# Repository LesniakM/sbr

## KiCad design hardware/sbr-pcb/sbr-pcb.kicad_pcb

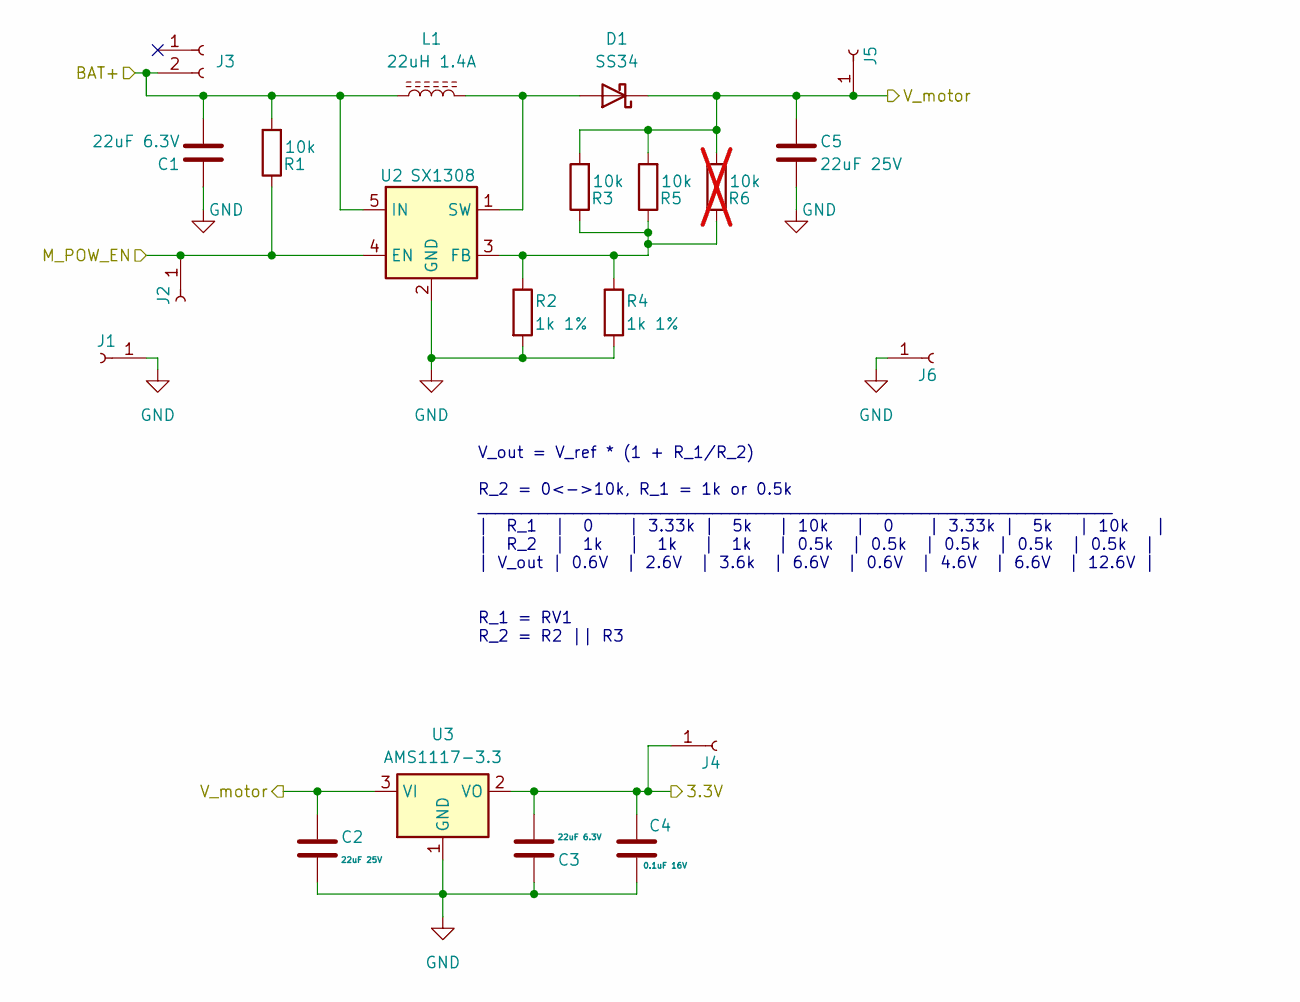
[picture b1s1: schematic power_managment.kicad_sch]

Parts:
C1, C3: 22uF 6.3V; C_0603_1608Metric; JLCPCB# C59461
C2, C5: 22uF 25V; C_0805_2012Metric; JLCPCB# C45783
C4: 0.1uF 16V; C_0402_1005Metric; JLCPCB# C1525
D1: SS34; D_SMA; JLCPCB# C8678
J1, J2, J4, J5, J6: Conn_hole; PinHeader_1x01_P2.54mm_Vertical
J3: Conn_01x02_Socket; PinHeader_1x02_P2.54mm_Vertical
L1: 22uH 1.4A; L_TDK_VLS6045EX_VLS6045AF; JLCPCB# C241601
R1, R3, R5: 10k; R_0603_1608Metric; JLCPCB# C25804
R2, R4: 1k 1%; R_0603_1608Metric; JLCPCB# C21190
R6: 10k; R_0603_1608Metric; JLCPCB# C25804; not fitted
U2: SX1308; SOT-23-6; LCSC Part # C78162
U3: AMS1117-3.3; SOT-223-3_TabPin2; JLCPCB# C6186

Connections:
/IMU/3.3V: C3.2, C4.1, J4.1, U3.2 (VO); also elsewhere on the board
/MCU/BAT+: C1.2, J3.2, L1.1, R1.2, U2.5 (IN); also elsewhere on the board
/MCU/M_POW_EN: J2.1, R1.1, U2.4 (EN); also elsewhere on the board
/motor_control/V_motor: C2.1, C5.1, D1.1 (K), J5.1, R3.2, R5.2, R6.2, U3.3 (VI); also elsewhere on the board
GND: C1.1, C2.2, C3.1, C4.2, C5.2, J1.1, J6.1, R2.2, R4.2, U2.2 (GND), U3.1 (GND); also elsewhere on the board
unnamed: D1.2 (A), L1.2, U2.1 (SW)
unnamed: R2.1, R3.1, R4.1, R5.1, R6.1, U2.3 (FB)

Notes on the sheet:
V_out = V_ref * (1 + R_1/R_2) R_2 = 0<->10k, R_1 = 1k or 0.5k _________________________________________________________________________ | R_1 | 0 | 3.33k | 5k | 10k | 0 | 3.33k | 5k | 10k | | R_2 | 1k | 1k | 1k | 0.5k | 0.5k | 0.5k | 0.5k | 0.5k | | V_out | 0.6V | 2.6V | 3.6k | 6.6V | 0.6V | 4.6V |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

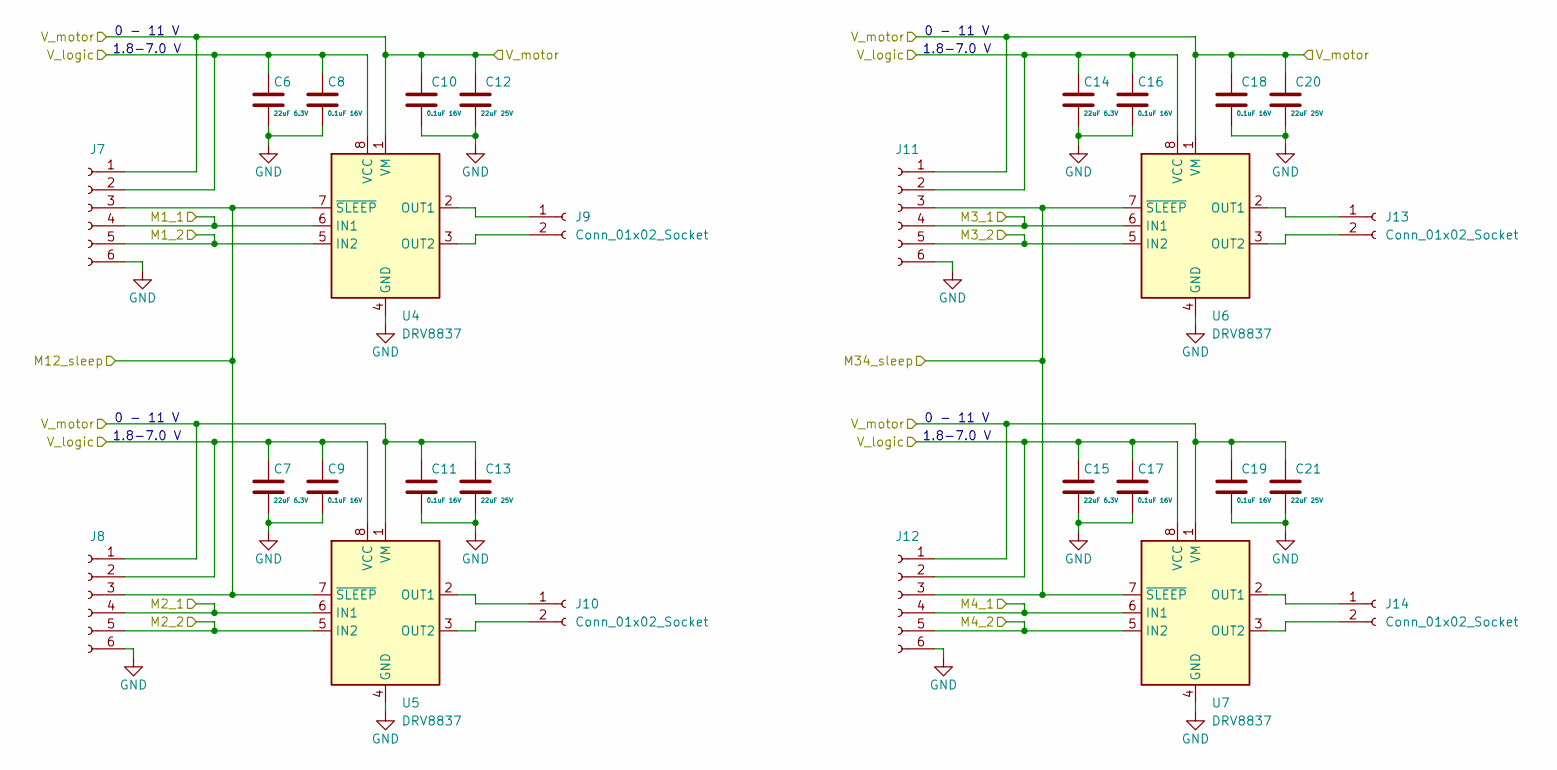
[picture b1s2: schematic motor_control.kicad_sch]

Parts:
C6, C7, C14, C15: 22uF 6.3V; C_0603_1608Metric; JLCPCB# C59461
C8, C9, C10, C11, C16, C17, C18, C19: 0.1uF 16V; C_0402_1005Metric; JLCPCB# C1525
C12, C13, C20, C21: 22uF 25V; C_0805_2012Metric; JLCPCB# C45783
J7, J8, J11, J12: Conn_01x06_Socket; PinHeader_1x06_P1.27mm_Vertical
J9, J10, J13, J14: Conn_01x02_Socket; PinSocket_1x02_P2.54mm_Vertical
U4, U5, U6, U7: DRV8837; WSON-8-1EP_2x2mm_P0.5mm_EP0.9x1.6mm; JLCPCB# C39159

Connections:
/IMU/3.3V: C6.1, C7.1, C8.1, C9.1, C14.1, C15.1, C16.1, C17.1, J7.2, J8.2, J11.2, J12.2, U4.8 (VCC), U5.8 (VCC), U6.8 (VCC), U7.8 (VCC); also elsewhere on the board
/MCU/M1_1: J7.4, U4.6 (IN1); also elsewhere on the board
/MCU/M1_2: J7.5, U4.5 (IN2); also elsewhere on the board
/MCU/M2_1: J8.4, U5.6 (IN1); also elsewhere on the board
/MCU/M2_2: J8.5, U5.5 (IN2); also elsewhere on the board
/MCU/M3_1: J11.4, U6.6 (IN1); also elsewhere on the board
/MCU/M3_2: J11.5, U6.5 (IN2); also elsewhere on the board
/MCU/M4_1: J12.4, U7.6 (IN1); also elsewhere on the board
/MCU/M4_2: J12.5, U7.5 (IN2); also elsewhere on the board
/MCU/M12_sleep: J7.3, J8.3, U4.7 (~SLEEP), U5.7 (~SLEEP); also elsewhere on the board
/MCU/M34_sleep: J11.3, J12.3, U6.7 (~SLEEP), U7.7 (~SLEEP); also elsewhere on the board
/motor_control/V_motor: C10.1, C11.1, C12.1, C13.1, C18.1, C19.1, C20.1, C21.1, J7.1, J8.1, J11.1, J12.1, U4.1 (VM), U5.1 (VM), U6.1 (VM), U7.1 (VM); also elsewhere on the board
GND: C6.2, C7.2, C8.2, C9.2, C10.2, C11.2, C12.2, C13.2, C14.2, C15.2, C16.2, C17.2, C18.2, C19.2, C20.2, C21.2, J7.6, J8.6, J11.6, J12.6, U4.4 (GND), U4.9 (GND), U5.4 (GND), U5.9 (GND), U6.4 (GND), U6.9 (GND), U7.4 (GND), U7.9 (GND); also elsewhere on the board
unnamed: J9.1, U4.2 (OUT1)
unnamed: J9.2, U4.3 (OUT2)
unnamed: J10.1, U5.2 (OUT1)
unnamed: J10.2, U5.3 (OUT2)
unnamed: J13.1, U6.2 (OUT1)
unnamed: J13.2, U6.3 (OUT2)
unnamed: J14.1, U7.2 (OUT1)
unnamed: J14.2, U7.3 (OUT2)

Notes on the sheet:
1.8-7.0 V
0 - 11 V

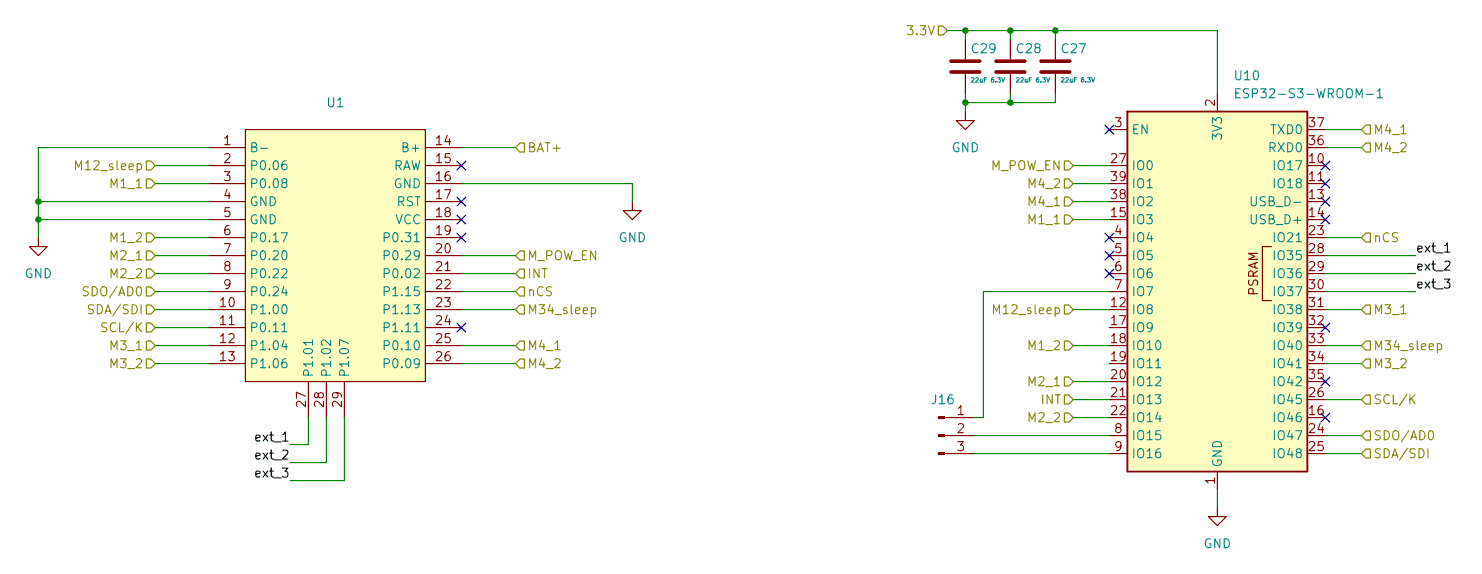
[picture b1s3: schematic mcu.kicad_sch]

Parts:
C27, C28, C29: 22uF 6.3V; C_0603_1608Metric; JLCPCB# C59461
J16: Conn_01x03_Pin; PinHeader_1x03_P2.54mm_Vertical
U1: ProMicro_nRF52840
U10: ESP32-S3-WROOM-1

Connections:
/IMU/3.3V: C27.1, C28.1, C29.1, U10.2 (3V3); also elsewhere on the board
/IMU/INT: U1.21 (P0.02), U10.21 (IO13); also elsewhere on the board
/IMU/SCL/K: U1.11 (P0.11), U10.26 (IO45); also elsewhere on the board
/IMU/SDA/SDI: U1.10 (P1.00), U10.25 (IO48); also elsewhere on the board
/IMU/SDO/AD0: U1.9 (P0.24), U10.24 (IO47); also elsewhere on the board
/IMU/nCS: U1.22 (P1.15), U10.23 (IO21); also elsewhere on the board
/MCU/BAT+: U1.14 (B+); also elsewhere on the board
/MCU/M1_1: U1.3 (P0.08), U10.15 (IO3); also elsewhere on the board
/MCU/M1_2: U1.6 (P0.17), U10.18 (IO10); also elsewhere on the board
/MCU/M2_1: U1.7 (P0.20), U10.20 (IO12); also elsewhere on the board
/MCU/M2_2: U1.8 (P0.22), U10.22 (IO14); also elsewhere on the board
/MCU/M3_1: U1.12 (P1.04), U10.31 (IO38); also elsewhere on the board
/MCU/M3_2: U1.13 (P1.06), U10.34 (IO41); also elsewhere on the board
/MCU/M4_1: U1.25 (P0.10), U10.37 (TXD0), U10.38 (IO2); also elsewhere on the board
/MCU/M4_2: U1.26 (P0.09), U10.36 (RXD0), U10.39 (IO1); also elsewhere on the board
/MCU/M12_sleep: U1.2 (P0.06), U10.12 (IO8); also elsewhere on the board
/MCU/M34_sleep: U1.23 (P1.13), U10.33 (IO40); also elsewhere on the board
/MCU/M_POW_EN: U1.20 (P0.29), U10.27 (IO0); also elsewhere on the board
/MCU/ext_1: U1.27 (P1.01), U10.28 (IO35)
/MCU/ext_2: U1.28 (P1.02), U10.29 (IO36)
/MCU/ext_3: U1.29 (P1.07), U10.30 (IO37)
GND: C27.2, C28.2, C29.2, U1.1 (B-), U1.4 (GND), U1.5 (GND), U1.16 (GND), U10.1 (GND), U10.40 (GND), U10.41 (GND); also elsewhere on the board
unnamed: J16.1, U10.7 (IO7)
unnamed: J16.2, U10.8 (IO15)
unnamed: J16.3, U10.9 (IO16)

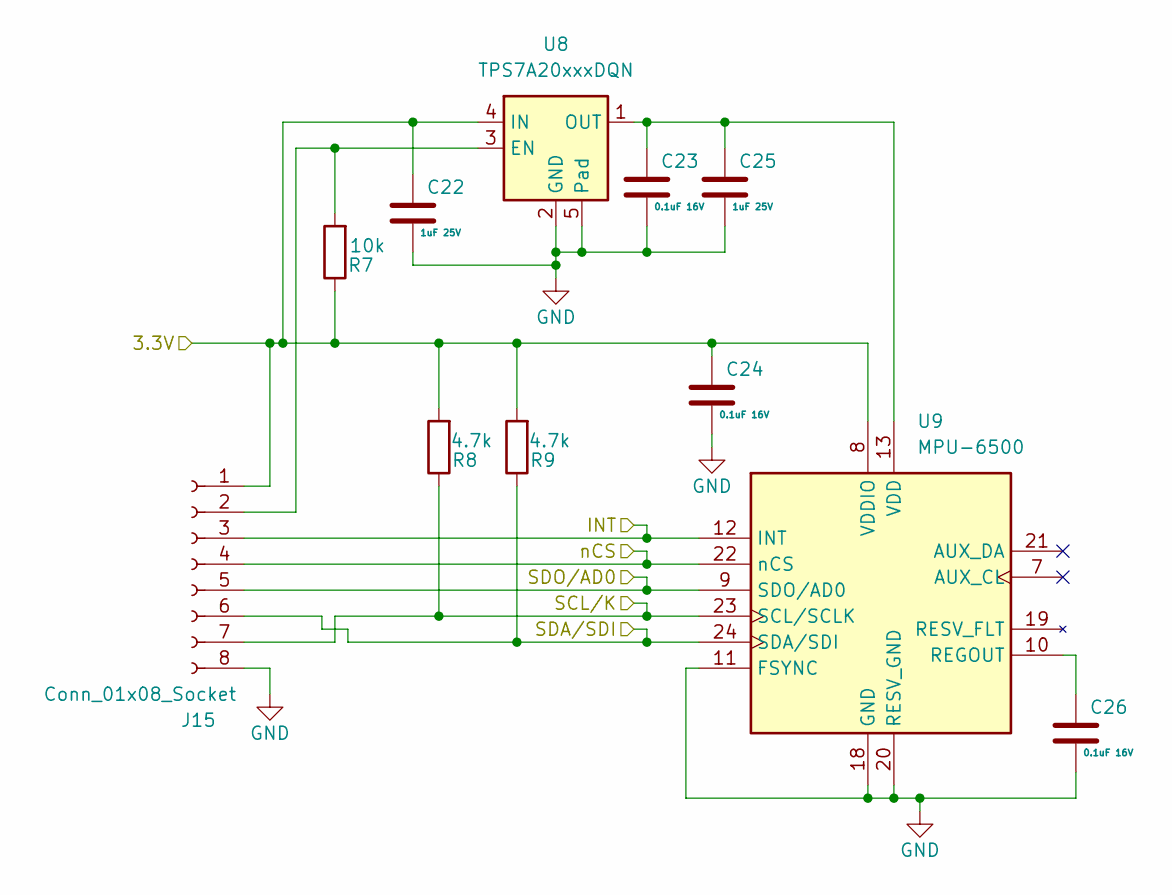
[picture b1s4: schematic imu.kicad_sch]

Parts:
C22, C25: 1uF 25V; C_0402_1005Metric; JLCPCB# C52923
C23, C24, C26: 0.1uF 16V; C_0402_1005Metric; JLCPCB# C1525
J15: Conn_01x08_Socket; PinSocket_1x08_P2.54mm_Vertical
R7: 10k; R_0603_1608Metric; JLCPCB# C25804
R8, R9: 4.7k; R_0603_1608Metric; JLCPCB# C23162
U8: TPS7A20xxxDQN; Texas_X2SON-4_1x1mm_P0.65mm; JLCPCB# C2878130
U9: MPU-6500; InvenSense_QFN-24_3x3mm_P0.4mm; JLCPCB# C50278

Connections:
/IMU/3.3V: C22.1, C24.1, J15.1, R7.1, R8.2, R9.2, U8.4 (IN), U9.8 (VDDIO); also elsewhere on the board
/IMU/INT: J15.3, U9.12 (INT); also elsewhere on the board
/IMU/SCL/K: J15.7, R8.1, U9.23 (SCL/SCLK); also elsewhere on the board
/IMU/SDA/SDI: J15.6, R9.1, U9.24 (SDA/SDI); also elsewhere on the board
/IMU/SDO/AD0: J15.5, U9.9 (SDO/AD0); also elsewhere on the board
/IMU/nCS: J15.4, U9.22 (nCS); also elsewhere on the board
GND: C22.2, C23.2, C24.2, C25.2, C26.2, J15.8, U8.2 (GND), U8.5 (Pad), U9.11 (FSYNC), U9.18 (GND), U9.20 (RESV_GND); also elsewhere on the board
unnamed: J15.2, R7.2, U8.3 (EN)
unnamed: C26.1, U9.10 (REGOUT)

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
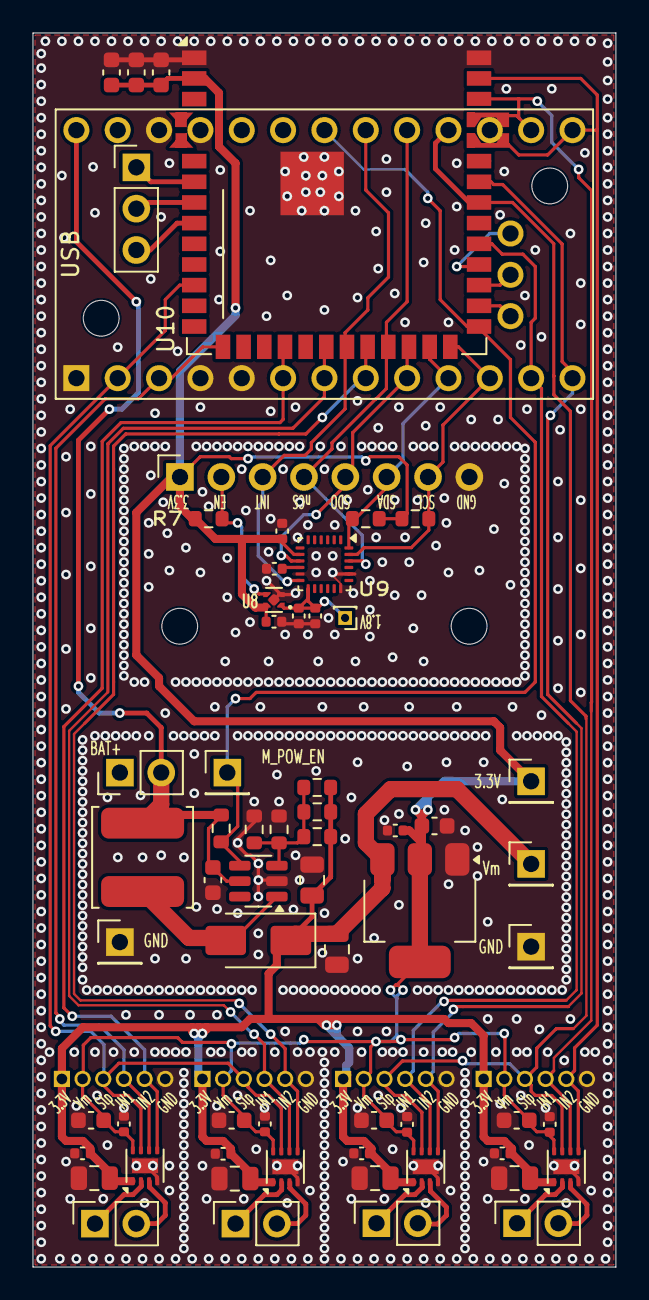
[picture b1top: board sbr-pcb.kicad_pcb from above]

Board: 2 copper layers, 35.8 x 75.8 mm, 66 parts (0 on the bottom side), 39 nets.

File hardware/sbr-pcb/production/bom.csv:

Designator,Footprint,Quantity,Value,LCSC Part #
"C1, C14, C15, C27, C28, C29, C3, C6, C7",0603,9,22uF 6.3V,C59461
"C10, C11, C16, C17, C18, C19, C23, C24, C26, C4, C8, C9",0402,12,0.1uF 16V,C1525
"C12, C13, C2, C20, C21, C5",0805,6,22uF 25V,C45783
"C22, C25",0402,2,1uF 25V, C52923
D1,D_SMA,1,SS34,C8678
"R1, R3, R5, R7",0603,4,10k,C25804
"R2, R4",0603,2,1k 1%,C21190
"R8, R9",0603,2,4.7k,C23162
U2,SOT-23-6,1,SX1308,C78162
U3,SOT-223-3_TabPin2,1,AMS1117-3.3,C6186
"U4, U5, U6, U7",WSON-8-1EP_2x2mm_P0.5mm_EP0.9x1.6mm,4,DRV8837,C39159
U8,Texas_X2SON-4_1x1mm_P0.65mm,1,TPS7A20xxxDQN,C2878130
U9,InvenSense_QFN-24_3x3mm_P0.4mm,1,MPU-6500,C50278

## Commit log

2025-09-14 Formating and error handling
2025-09-14 BLE stuff move to BLE files. Add build time info.
2025-12-14 Replace deprecated params
2025-12-14 Refactor and reimplement MPU6050
2025-12-15 IMU read in separate thread
